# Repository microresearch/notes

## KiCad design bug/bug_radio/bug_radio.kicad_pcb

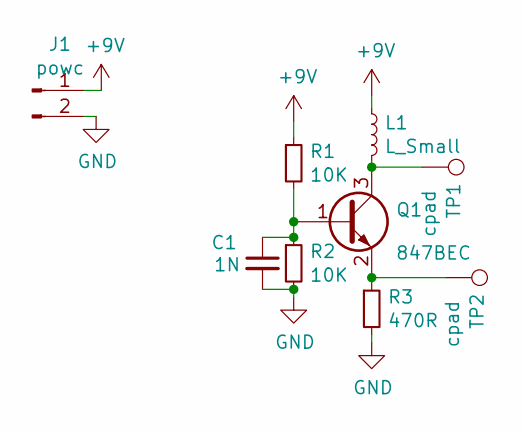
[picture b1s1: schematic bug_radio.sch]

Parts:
C1: 1N; C_0805_HandSoldering
J1: powc; Pin_Header_Straight_1x02_Pitch2.54mm
L1: L_Small; Pin_Header_Straight_1x02_Pitch2.54mm_SMD_Pin1Left
Q1: 847BEC; SOT-23
R1, R2: 10K; R_0805_HandSoldering
R3: 470R; R_0805_HandSoldering
TP1, TP2: cpad; Pin_Header_Straight_1x01_Pitch2.54mm

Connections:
+9V: J1.1, L1.1, R1.1
GND: C1.2, J1.2, R2.2, R3.2
unnamed: C1.1, Q1.1 (B), R1.2, R2.1
unnamed: L1.2, Q1.3 (C), TP1.1
unnamed 4: Q1.2 (E), R3.1, TP2.1; also elsewhere on the board

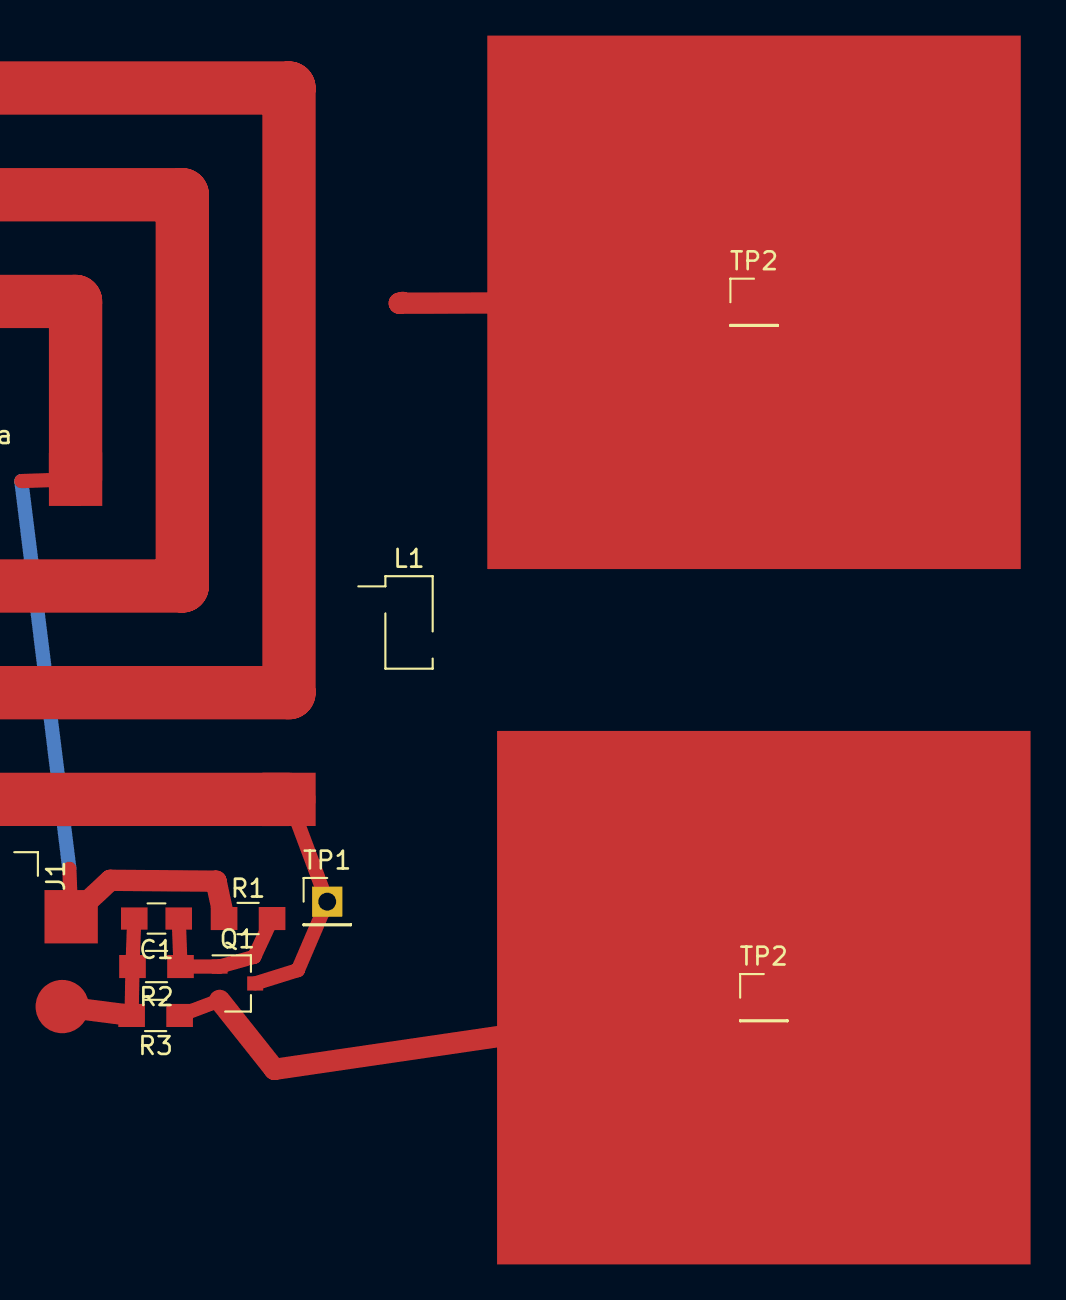
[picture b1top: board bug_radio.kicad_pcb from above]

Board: 2 copper layers, 10 parts (0 on the bottom side), 5 nets.

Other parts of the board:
TP2#2: cpad; Pin_Header_Straight_1x01_Pitch2.54mm

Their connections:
unnamed 4: TP2#2.1; also elsewhere on the board

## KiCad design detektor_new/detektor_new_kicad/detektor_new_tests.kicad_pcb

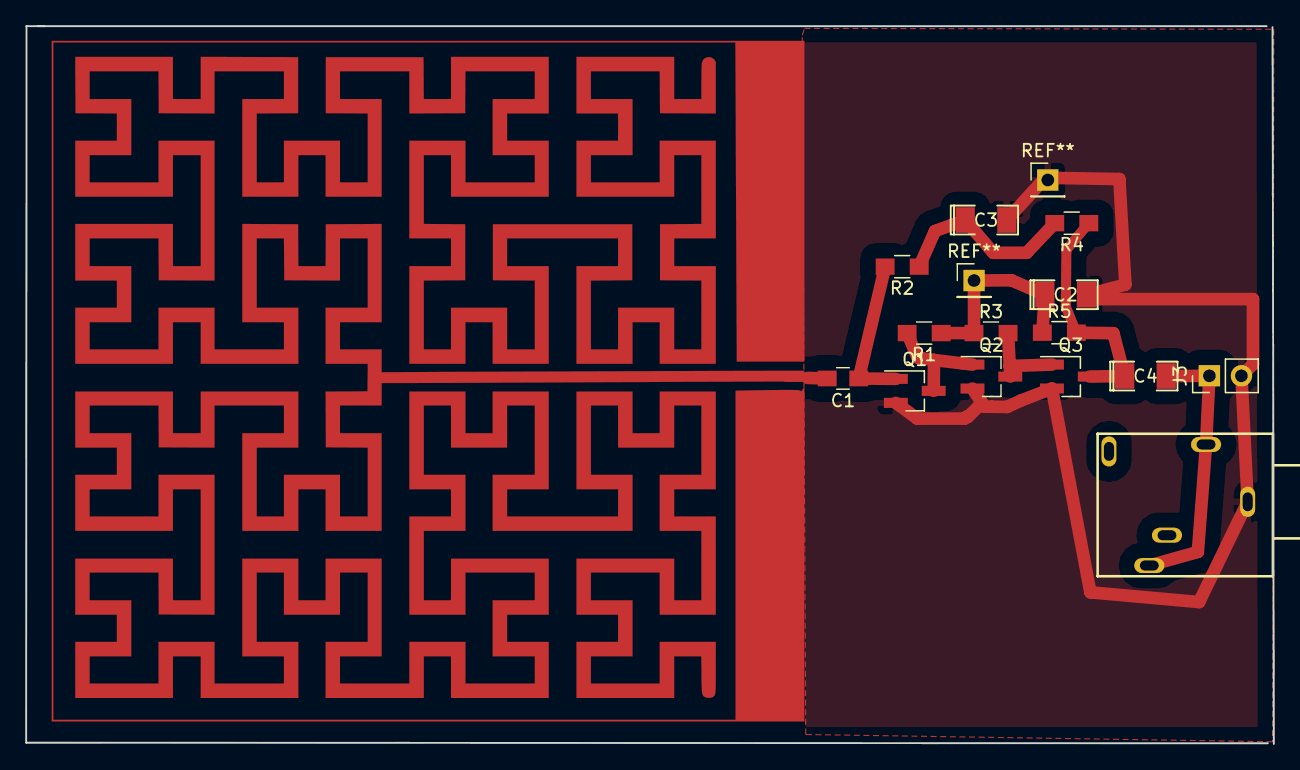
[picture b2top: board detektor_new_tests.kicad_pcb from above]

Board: 2 copper layers, 99.0 x 56.9 mm, 14 parts (0 on the bottom side), 8 nets.

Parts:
C1: 100n; C_0805_HandSoldering
C2, C3, C4: 10u; SMD-1206_Pol
J3: OUT; Pin_Header_Straight_1x02_Pitch2.54mm
Q1: 517-BEC; SOT-23_Handsoldering
Q2, Q3: 847-BEC; SOT-23_Handsoldering
R1, R3: 10K; R_0805_HandSoldering
R2, R4: 100K; R_0805_HandSoldering
R5: 1K; R_0805_HandSoldering
X1: 1503_09

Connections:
GND: C2.2, C3.2, J3.2, Q1.2, Q2.2, Q3.2, X1.1
unnamed: C1.1, Q1.1, R2.2
unnamed: C2.1, R1.1, R3.1, R5.1
unnamed: C3.1, R2.1, R4.2
unnamed: C4.1, Q3.3, R4.1, R5.2
unnamed: C4.2, J3.1, X1.2, X1.3
unnamed: Q1.3, Q2.1, R1.2
unnamed: Q2.3, Q3.1, R3.2

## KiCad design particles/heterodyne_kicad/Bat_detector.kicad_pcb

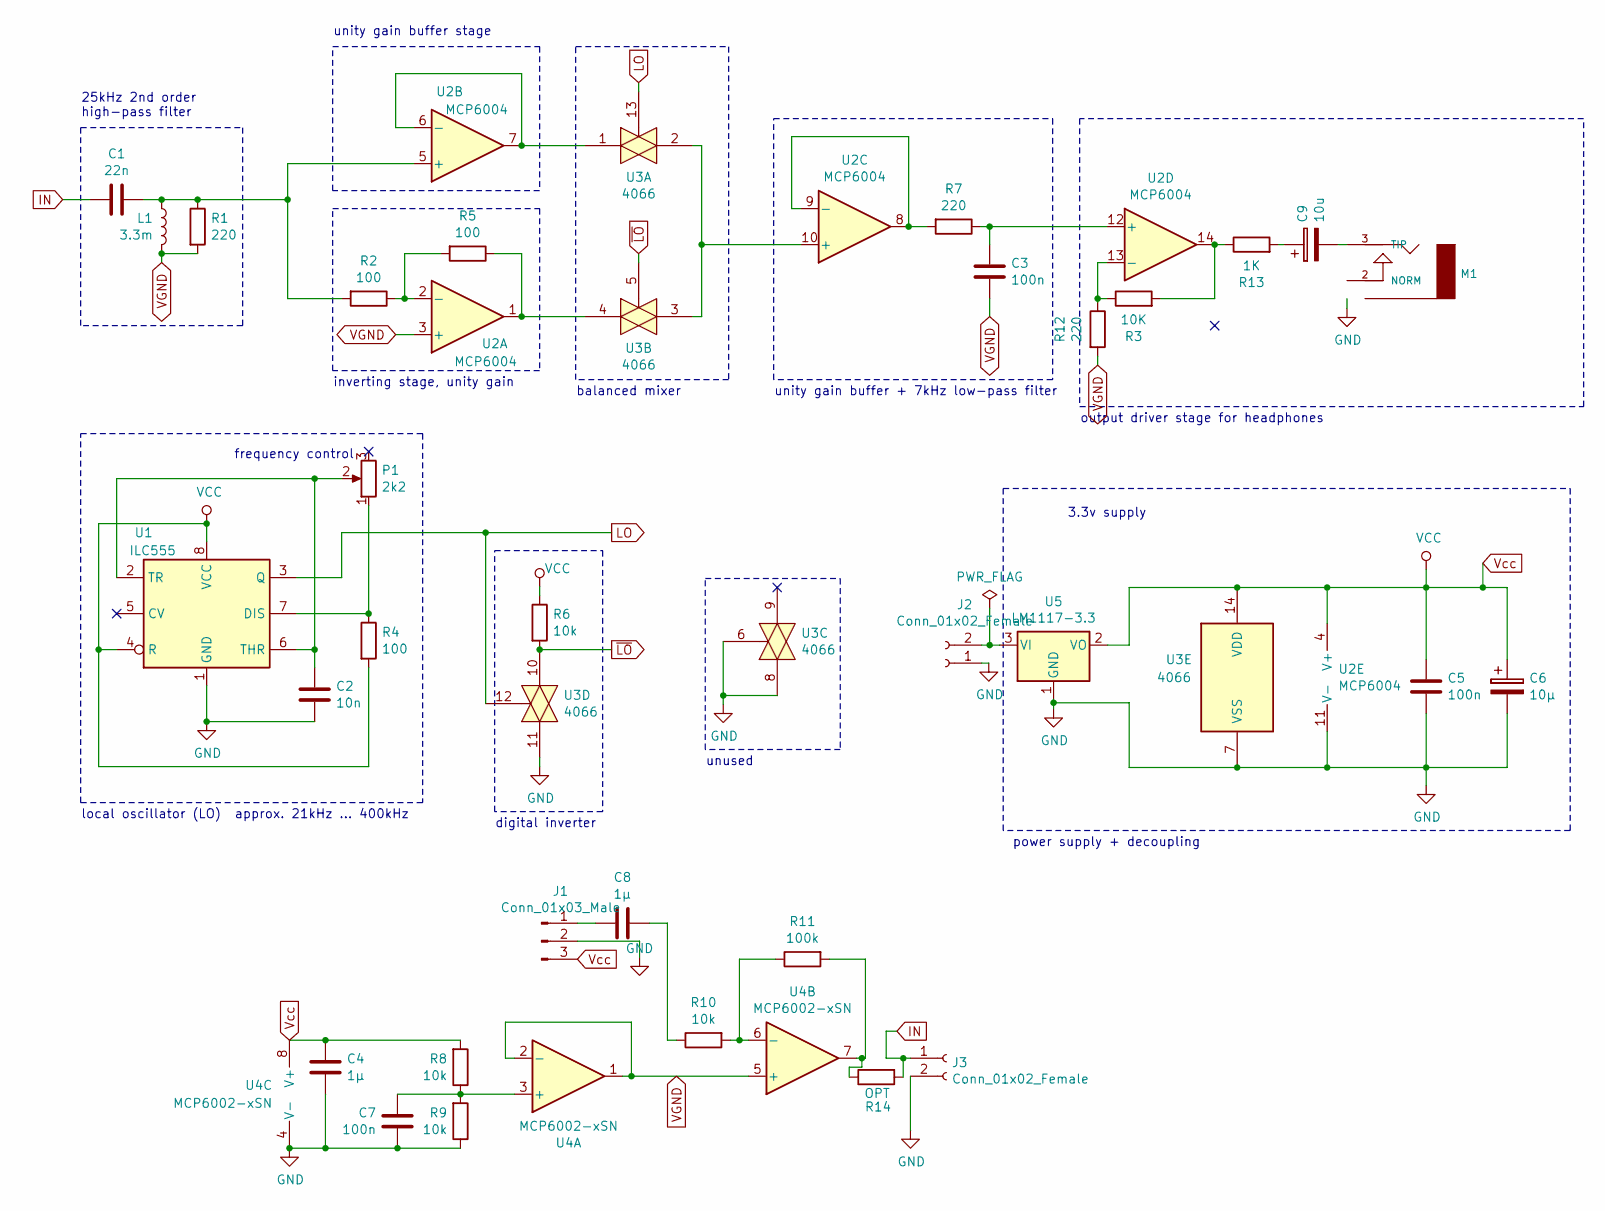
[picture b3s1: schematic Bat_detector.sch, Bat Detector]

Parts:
C1: 22n; C_0805_HandSoldering
C2: 10n; C_0805_HandSoldering
C3, C5, C7: 100n; C_0805_HandSoldering
C4, C8: 1µ; SMD-1206_Pol
C6: 10µ; SMD-1206_Pol
C9: 10u; SMD-1206_Pol
J1: Conn_01x03_Male; Pin_Header_Straight_1x03_Pitch2.54mm
J2, J3: Conn_01x02_Female; Pin_Header_Straight_1x02_Pitch2.54mm
L1: 3.3m; L_Wuerth_HCI-5040
M1: AUDIO-JACKERTHENVAR-PJ398; Jack_3.5mm_QingPu_WQP-PJ398SM_Vertical_CircularHoles
P1: 2k2; Potentiometer_Trimmer_Piher_PT-10v10_Horizontal_Px10.0mm_Py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
R1, R7, R12: 220; R_0805_HandSoldering
R2, R4, R5: 100; R_0805_HandSoldering
R3: 10K; R_0805_HandSoldering
R6, R8, R9, R10: 10k; R_0805_HandSoldering
R11: 100k; R_0805_HandSoldering
R13: 1K; R_0805_HandSoldering
R14: OPT; R_0805_HandSoldering
U1: ILC555; SOIC-8-N
U2: MCP6004; SOIC-14_N
U3: 4066; SOIC-14_N
U4: MCP6002-xSN; SOIC-8-N
U5: LM1117-3.3; TO-252-2_Rectifier

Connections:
GND: C2.2, C4.2, C5.2, C6.2, C7.1, J1.2, J2.1, J3.2, M1.1 (RING), R9.1, U1.1 (GND), U2.11 (V-), U3.6, U3.7 (VSS), U3.8, U3.11, U4.4 (V-), U5.1 (GND)
IN: C1.2, J3.1, R14.2
LO: U1.3 (Q), U3.12, U3.13
unnamed: C1.1, L1.2, R1.1, R2.2, U2.5 (+)
unnamed: C2.1, P1.2, U1.2 (TR), U1.6 (THR)
unnamed: C3.1, R7.1, U2.12 (+)
unnamed: C7.2, R8.1, R9.2, U4.3 (+)
unnamed: C8.1, J1.1
unnamed: C8.2, R10.1
unnamed: C9.1, R13.2
unnamed: C9.2, M1.3 (TIP)
unnamed: J2.2, U5.3 (VI)
unnamed: P1.1, R4.1, U1.7 (DIS)
unnamed: R2.1, R5.2, U2.2 (-)
unnamed: R5.1, U2.1, U3.4
unnamed: R7.2, U2.8, U2.9 (-)
unnamed: R10.2, R11.1, U4.6 (-)
unnamed: R11.2, R14.1, U4.7
unnamed: R3.1, R12.1, U2.13 (-)
unnamed: R3.2, R13.1, U2.14
unnamed: U2.6 (-), U2.7, U3.1
unnamed: U2.10 (+), U3.2, U3.3
VGND: C3.2, L1.1, R1.2, R12.2, U2.3 (+), U4.1, U4.2 (-), U4.5 (+)
Vcc: C4.1, C5.1, C6.1, J1.3, R4.2, R6.1, R8.2, U1.4 (R), U1.8 (VCC), U2.4 (V+), U3.14 (VDD), U4.8 (V+), U5.2 (VO)
~LO: R6.2, U3.5, U3.10

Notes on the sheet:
25kHz 2nd order high-pass filter
inverting stage, unity gain
local oscillator (LO) approx. 21kHz ... 400kHz
digital inverter
unused
balanced mixer
unity gain buffer stage
unity gain buffer + 7kHz low-pass filter
output driver stage for headphones
frequency control
power supply + decoupling
3.3v supply

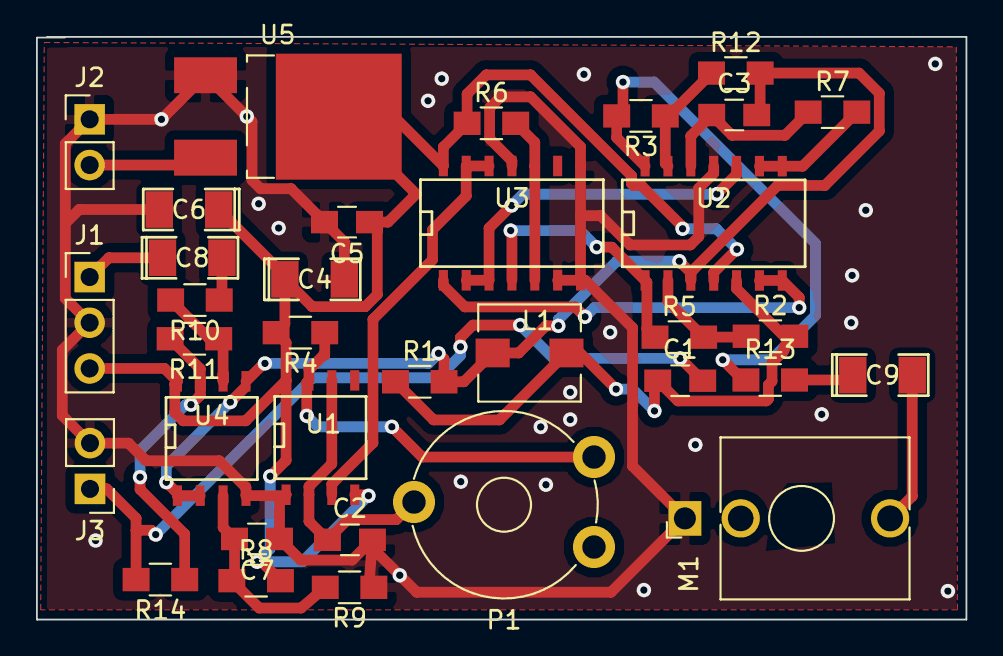
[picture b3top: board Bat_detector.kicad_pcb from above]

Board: 2 copper layers, 51.6 x 32.4 mm, 34 parts (0 on the bottom side), 25 nets.

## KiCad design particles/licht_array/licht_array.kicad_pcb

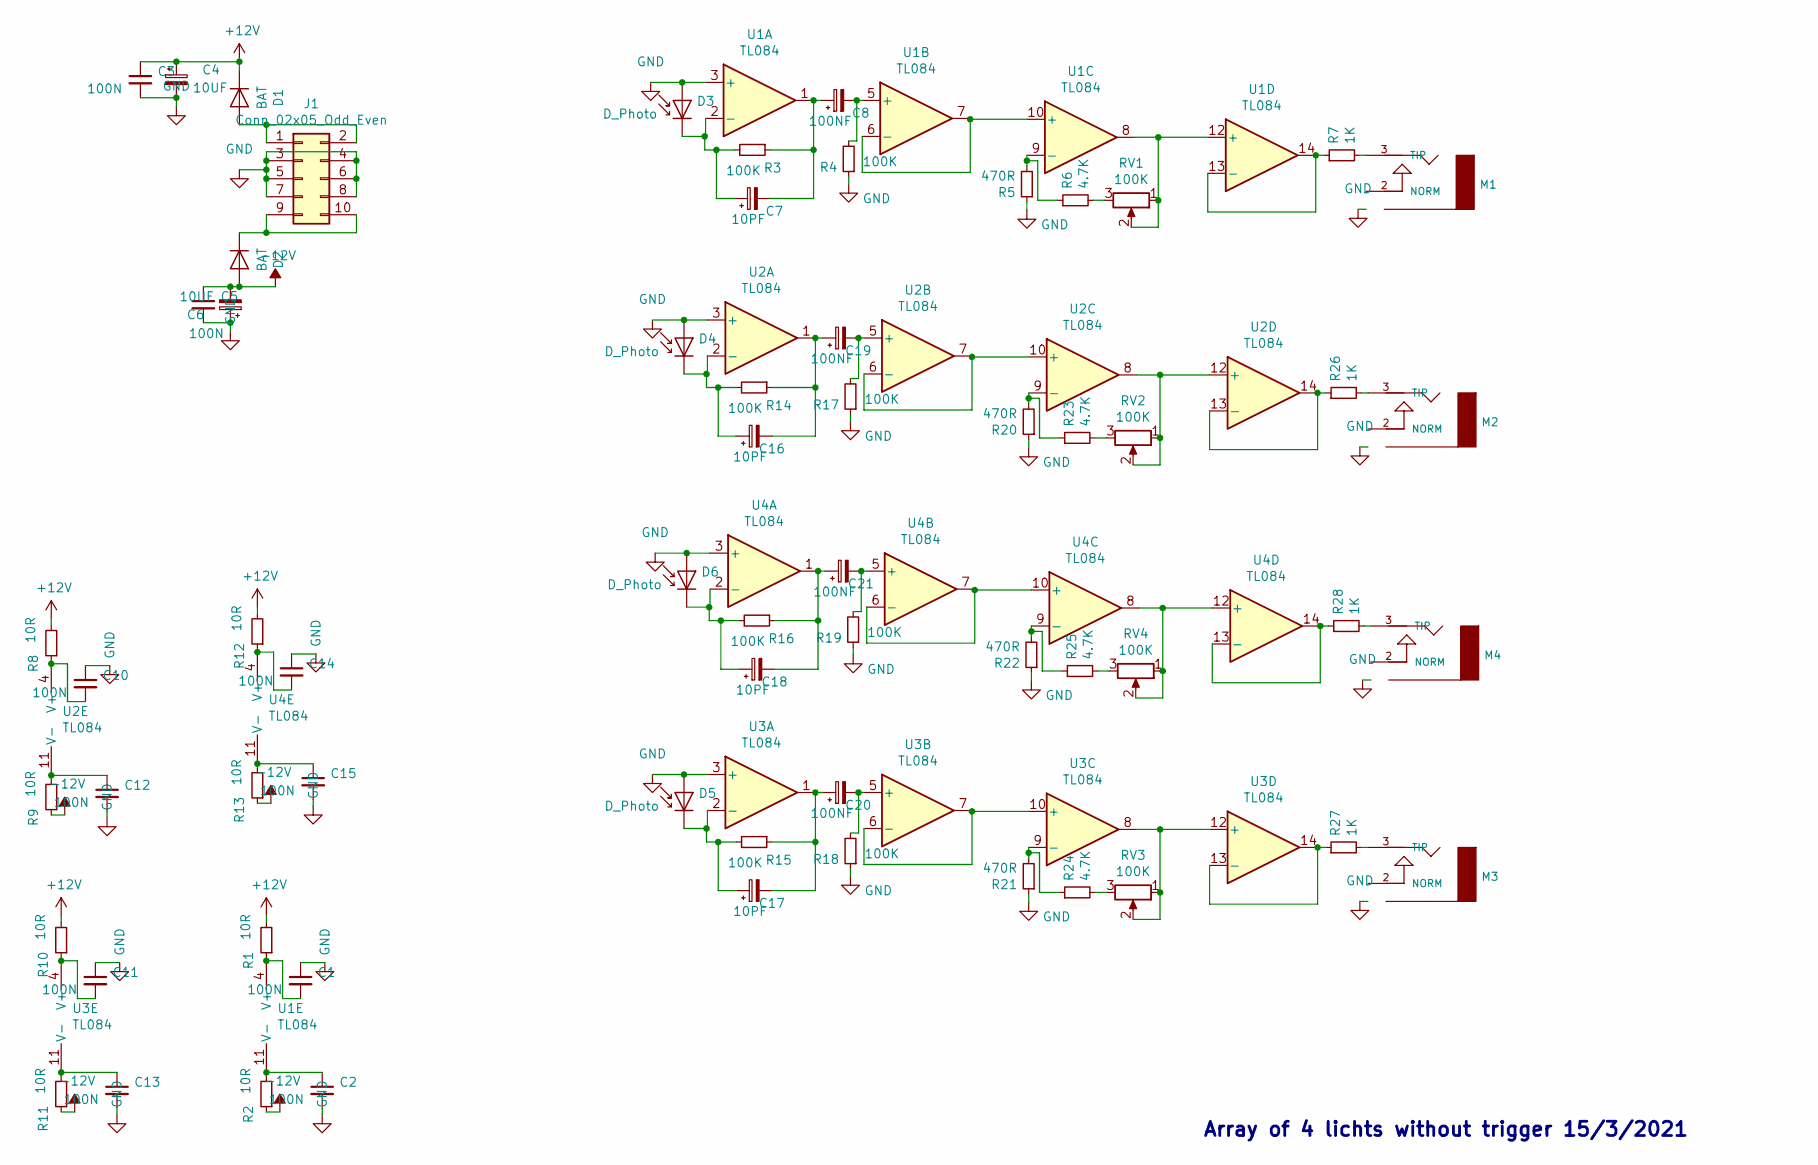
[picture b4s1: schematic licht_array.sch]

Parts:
C1, C2, C3, C5, C10, C11, C12, C13, C14, C15: 100N; C_0805_HandSoldering
C4, C6: 10UF; SMD-1206_Pol
C7, C16, C17, C18: 10PF; C_0805_HandSoldering
C8, C19, C20, C21: 100NF; C_0805_HandSoldering
D1, D2: BAT; D_SOD-123
D3, D4, D5, D6: D_Photo; PhotoDiode_BPW82
J1: Conn_02x05_Odd_Even; Pin_Header_Straight_2x05_Pitch2.54mm
M1, M2, M3, M4: AUDIO-JACKERTHENVAR; Jack_3.5mm_QingPu_WQP-PJ398SM_Vertical_CircularHoles
R1, R2, R8, R9, R10, R11, R12, R13: 10R; R_0805_HandSoldering
R3, R4, R14, R15, R16, R17, R18, R19: 100K; R_0805_HandSoldering
R5, R20, R21, R22: 470R; R_0805_HandSoldering
R6, R23, R24, R25: 4.7K; R_0805_HandSoldering
R7, R26, R27, R28: 1K; R_0805_HandSoldering
RV1, RV2, RV3, RV4: 100K; Potentiometer_Trimmer_Piher_PT-10v10_Horizontal_Px10.0mm_Py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
U1, U2, U3, U4: TL084; SOIC-14_N

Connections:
+12V: C3.1, C4.1, D1.1 (K), R1.2, R8.2, R10.2, R12.2
-12V: C5.1, C6.2, D2.2 (A), R2.1, R9.1, R11.1, R13.1
GND: C1.1, C2.2, C3.2, C4.2, C5.2, C6.1, C10.1, C11.1, C12.2, C13.2, C14.1, C15.2, D3.2 (A), D4.2 (A), D5.2 (A), D6.2 (A), J1.3, J1.4, J1.5, J1.6, J1.7, J1.8, M1.1 (RING), M2.1 (RING), M3.1 (RING), M4.1 (RING), R4.1, R5.1, R17.1, R18.1, R19.1, R20.1, R21.1, R22.1, U1.3 (+), U2.3 (+), U3.3 (+), U4.3 (+)
unnamed: C1.2, R1.1, U1.4 (V+)
unnamed: C2.1, R2.2, U1.11 (V-)
unnamed: C7.1, D3.1 (K), R3.2, U1.2 (-)
unnamed: C7.2, C8.1, R3.1, U1.1
unnamed: C8.2, R4.2, U1.5 (+)
unnamed: C10.2, R8.1, U2.4 (V+)
unnamed: C11.2, R10.1, U3.4 (V+)
unnamed: C12.1, R9.2, U2.11 (V-)
unnamed: C13.1, R11.2, U3.11 (V-)
unnamed: C14.2, R12.1, U4.4 (V+)
unnamed: C15.1, R13.2, U4.11 (V-)
unnamed: C16.1, D4.1 (K), R14.2, U2.2 (-)
unnamed: C16.2, C19.1, R14.1, U2.1
unnamed: C17.1, D5.1 (K), R15.2, U3.2 (-)
unnamed: C17.2, C20.1, R15.1, U3.1
unnamed: C18.1, D6.1 (K), R16.2, U4.2 (-)
unnamed: C18.2, C21.1, R16.1, U4.1
unnamed: C19.2, R17.2, U2.5 (+)
unnamed: C20.2, R18.2, U3.5 (+)
unnamed: C21.2, R19.2, U4.5 (+)
unnamed: D1.2 (A), J1.1, J1.2
unnamed: D2.1 (K), J1.9, J1.10
unnamed: M1.3 (TIP), R7.2
unnamed: M2.3 (TIP), R26.2
unnamed: M3.3 (TIP), R27.2
unnamed: M4.3 (TIP), R28.2
unnamed: R5.2, R6.1, U1.9 (-)
unnamed: R6.2, RV1.3
unnamed: R7.1, U1.13 (-), U1.14
unnamed: R20.2, R23.1, U2.9 (-)
unnamed: R21.2, R24.1, U3.9 (-)
unnamed: R22.2, R25.1, U4.9 (-)
unnamed: R23.2, RV2.3
unnamed: R24.2, RV3.3
unnamed: R25.2, RV4.3
unnamed: R26.1, U2.13 (-), U2.14
unnamed: R27.1, U3.13 (-), U3.14
unnamed: R28.1, U4.13 (-), U4.14
unnamed: RV1.1, RV1.2, U1.8, U1.12 (+)
unnamed: RV2.1, RV2.2, U2.8, U2.12 (+)
unnamed: RV3.1, RV3.2, U3.8, U3.12 (+)
unnamed: RV4.1, RV4.2, U4.8, U4.12 (+)
unnamed: U1.6 (-), U1.7, U1.10 (+)
unnamed: U2.6 (-), U2.7, U2.10 (+)
unnamed: U3.6 (-), U3.7, U3.10 (+)
unnamed: U4.6 (-), U4.7, U4.10 (+)

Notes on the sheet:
Array of 4 lichts without trigger 15/3/2021

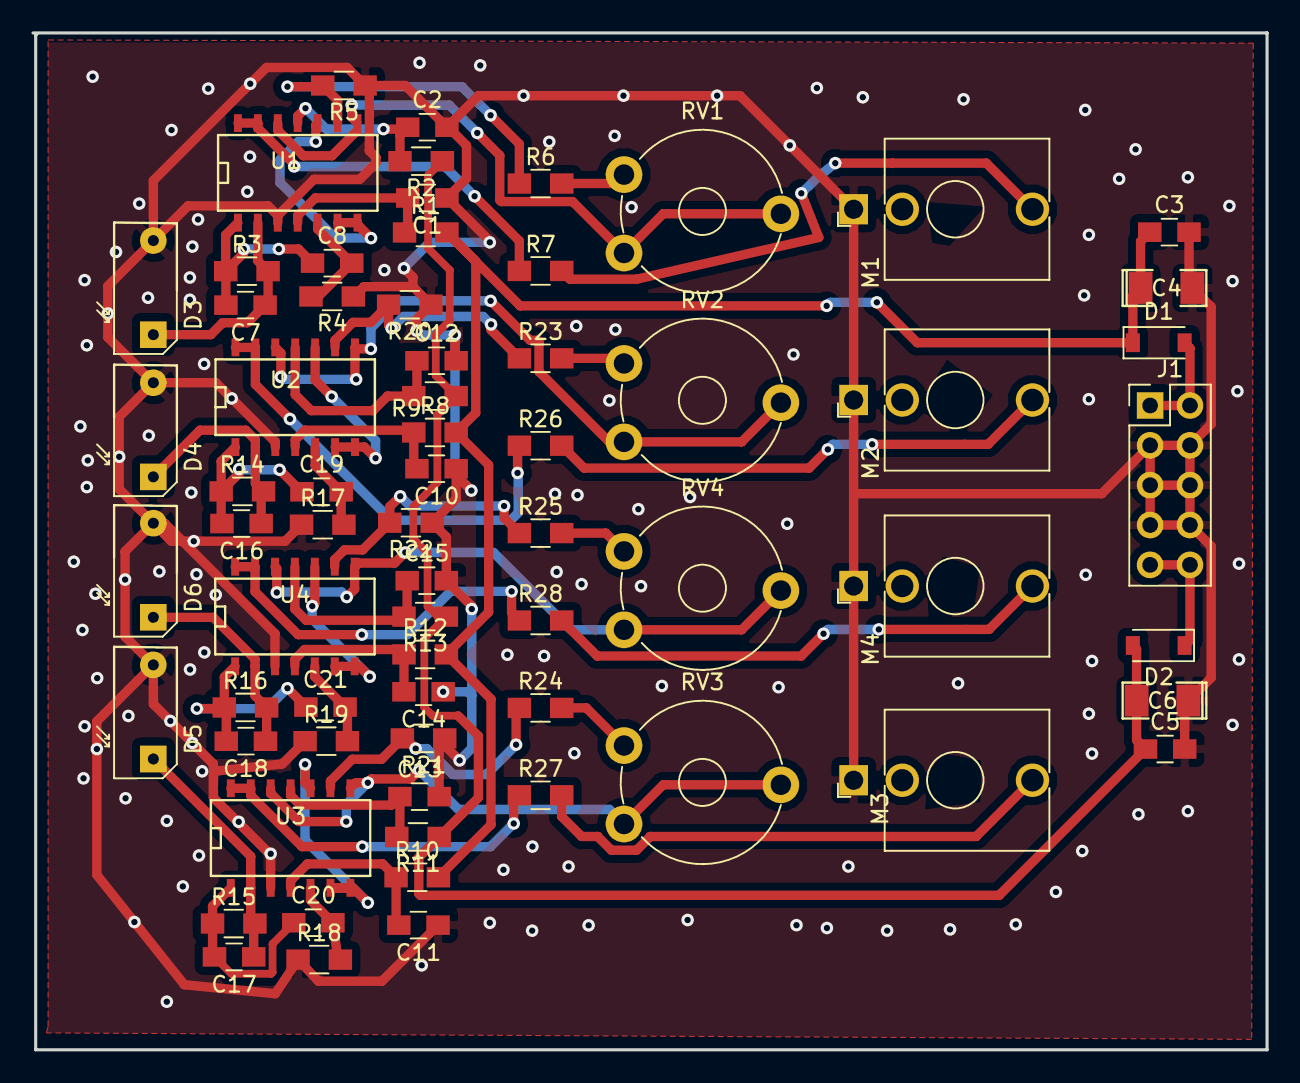
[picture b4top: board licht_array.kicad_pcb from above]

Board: 2 copper layers, 78.7 x 64.8 mm, 67 parts (0 on the bottom side), 49 nets.

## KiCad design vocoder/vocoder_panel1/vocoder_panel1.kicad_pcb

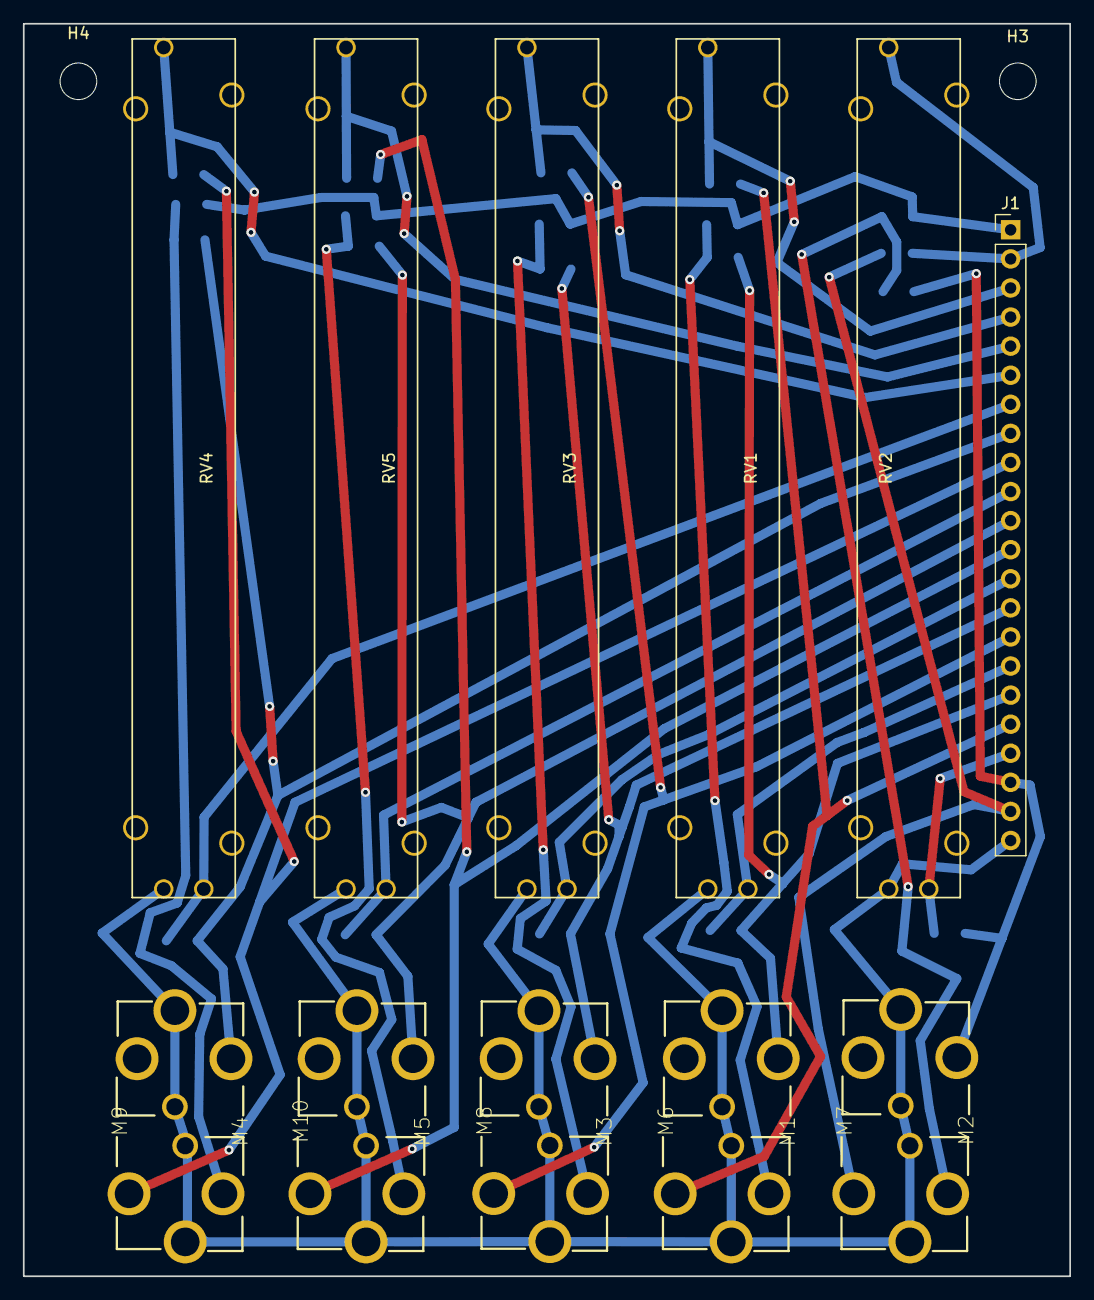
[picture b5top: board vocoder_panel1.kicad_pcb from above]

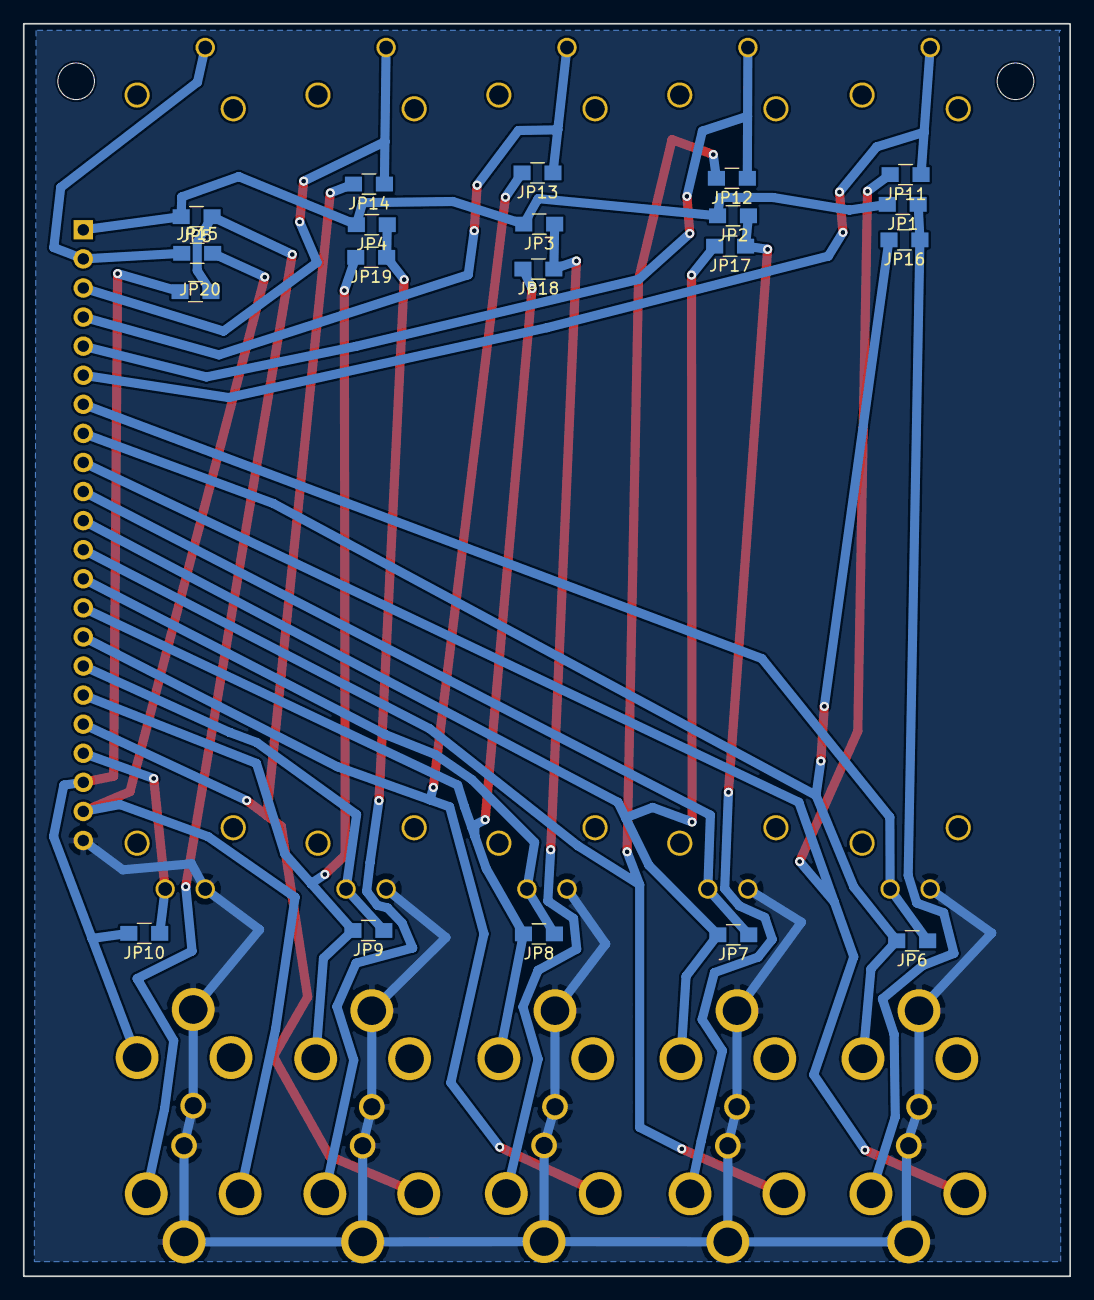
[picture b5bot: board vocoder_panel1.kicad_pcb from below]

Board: 2 copper layers, 91.4 x 109.4 mm, 38 parts (20 on the bottom side), 27 nets.

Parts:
H3, H4: MountingHole; MountingHole_3.2mm_M3
J1: Conn_01x22; Pin_Header_Straight_1x22_Pitch2.54mm
JP1, JP2, JP3, JP4, JP5, JP6, JP7, JP8, JP9, JP10, JP11, JP12, JP13, JP14, JP15, JP16, JP17, JP18, JP19, JP20: Jumper_NO_Small; R_0805_HandSoldering
M1, M2, M3, M4, M5, M6, M7, M8, M9, M10: AUDIO-JACKERTHENVAR; ERTHENVAR-JACK
RV1, RV3, RV4, RV5: R_POT; SMC-PTA6043-2015CPB103new
RV2: R_POT; SMC-PTA6043-2015CPB103

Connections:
/FB1: J1.7, JP6.1, RV4.1
/FB2: J1.10, JP7.1, RV5.1
/FB3: J1.13, JP8.1, RV3.1
/FB4: J1.16, JP9.1, RV1.1
/FB5: J1.19, JP10.1, RV2.1
/FB_1: J1.6, JP11.1, RV4.3
/FB_2: J1.5, JP12.1, RV5.3
/FB_3: J1.4, JP13.1, RV3.3
/FB_4: J1.3, JP14.1, RV1.3
/FB_5: J1.2, JP15.1, RV2.3
/J1: J1.8, JP6.2, JP16.2, M4.3
/J2: J1.11, JP7.2, JP17.2, M5.3
/J3: J1.14, JP8.2, JP18.2, M3.3
/J4: J1.17, JP9.2, JP19.2, M1.3
/J5: J1.20, JP10.2, JP20.2, M2.3
/JJ1: J1.9, JP11.2, M9.3
/JJ2: J1.12, JP12.2, M10.3
/JJ3: J1.15, JP13.2, M8.3
/JJ4: J1.18, JP14.2, M6.3
/JJ5: J1.21, JP15.2, M7.3
/NN1: JP1.1, JP16.1, M9.2
/NN2: JP2.1, JP17.1, M10.2
/NN3: JP3.1, JP18.1, M8.2
/NN4: JP4.1, JP19.1, M6.2
/NN5: JP5.1, JP20.1, M7.2
/PSBUS: J1.1, JP1.2, JP2.2, JP3.2, JP4.2, JP5.2
GND: J1.22, M1.1@1, M1.1@2, M2.1@1, M2.1@2, M3.1@1, M3.1@2, M4.1@1, M4.1@2, M5.1@1, M5.1@2, M6.1@1, M6.1@2, M7.1@1, M7.1@2, M8.1@1, M8.1@2, M9.1@1, M9.1@2, M10.1@1, M10.1@2, RV1.2, RV2.2, RV3.2, RV4.2, RV5.2

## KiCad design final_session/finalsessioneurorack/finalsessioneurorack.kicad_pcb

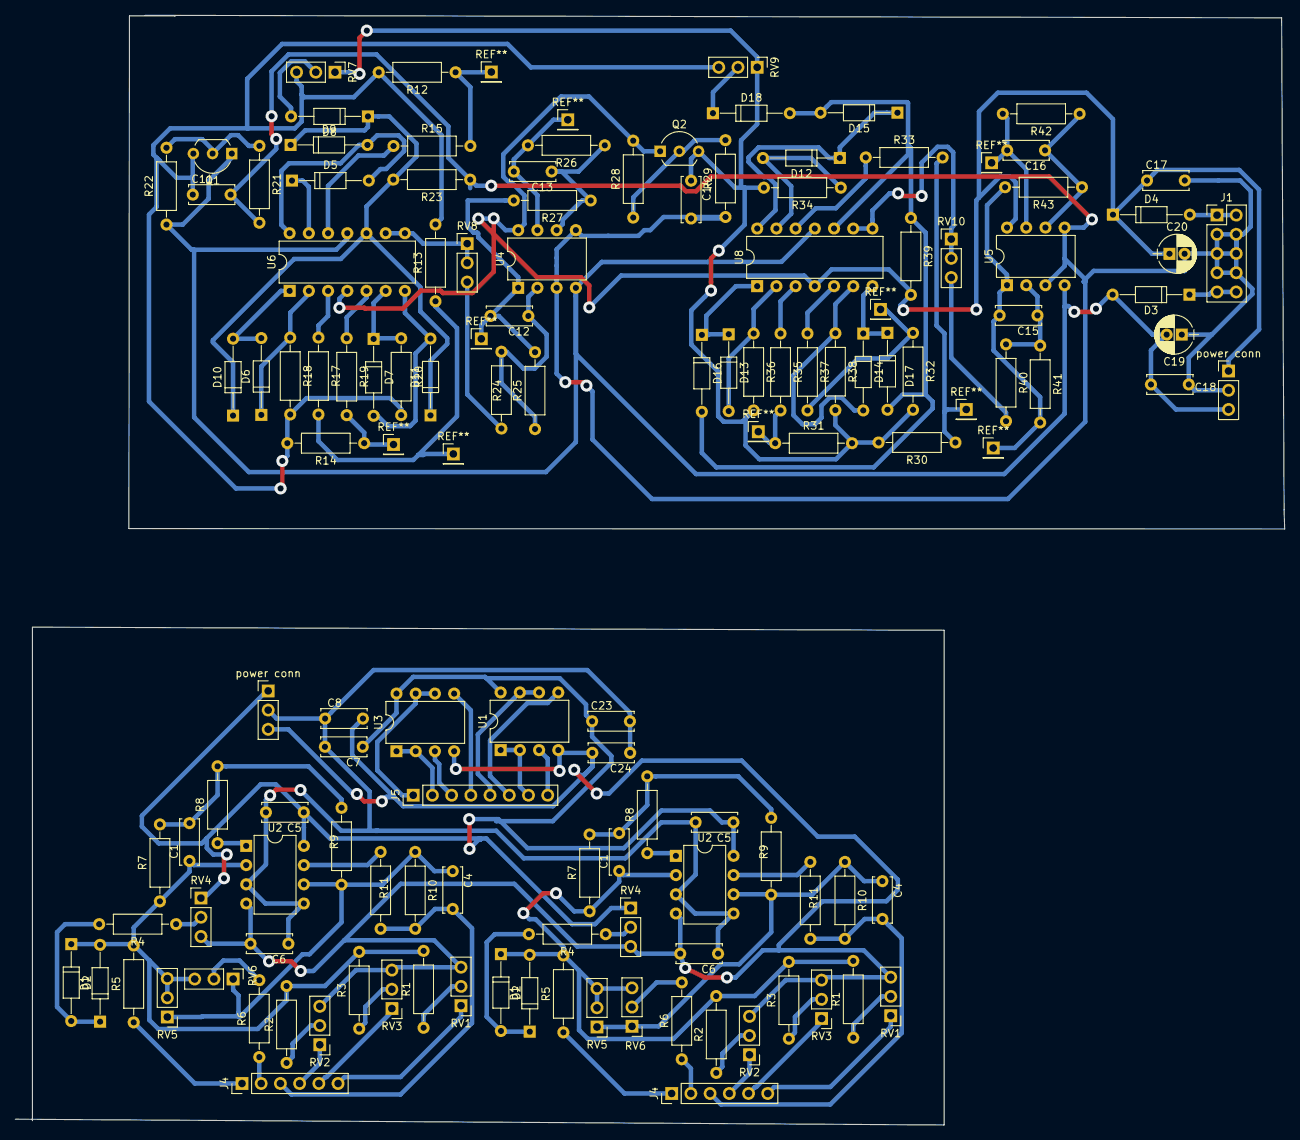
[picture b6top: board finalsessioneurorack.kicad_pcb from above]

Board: 2 copper layers, 167.8 x 146.7 mm, 127 parts (0 on the bottom side), 74 nets.

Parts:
C1, C1#2, C4, C4#2, C12, C13, C15, C16: 47pF; C_Disc_D6.0mm_W2.5mm_P5.00mm
C5, C5#2, C6, C6#2, C7, C8, C17, C18, C23, C24: 100n; C_Disc_D6.0mm_W2.5mm_P5.00mm
C11, C14: 100N; C_Disc_D6.0mm_W2.5mm_P5.00mm
C19, C20: 10uF; CP_Radial_D5.0mm_P2.00mm
D1, D1#2, D2, D2#2: BAT48; D_DO-35_SOD27_P10.16mm_Horizontal
D3, D4: D; D_DO-35_SOD27_P10.16mm_Horizontal
D5, D6, D7, D8, D9, D10, D11, D12, D13, D14, D15, D16, D17, D18: 1N4148; D_DO-35_SOD27_P10.16mm_Horizontal
J1: Conn_02x05_Odd_Even; Pin_Header_Straight_2x05_Pitch2.54mm
J4, J4#2: Conn_01x06_Male; Pin_Header_Straight_1x06_Pitch2.54mm
J5: Conn_01x08_Male; Pin_Header_Straight_1x08_Pitch2.54mm
Q1: BC557; TO-92_Inline_Wide
Q2: BC547; TO-92_Inline_Wide
R1, R1#2, R2, R2#2, R3, R3#2, R5, R5#2, R6, R6#2, R7, R7#2, R9, R9#2, R10, R10#2, R12, R13, R14, R30, R31, R32: 100K; R_Axial_DIN0207_L6.3mm_D2.5mm_P10.16mm_Horizontal
R4, R4#2: 270K; R_Axial_DIN0207_L6.3mm_D2.5mm_P10.16mm_Horizontal
R8, R8#2, R11, R11#2: 330R; R_Axial_DIN0207_L6.3mm_D2.5mm_P10.16mm_Horizontal
R15, R17, R18, R19, R20, R21, R23, R25, R26, R27, R29, R33, R34, R35, R36, R37, R38, R39, R41, R42, R43: 10K; R_Axial_DIN0207_L6.3mm_D2.5mm_P10.16mm_Horizontal
R22, R28: 2K2; R_Axial_DIN0207_L6.3mm_D2.5mm_P10.16mm_Horizontal
R24, R40: 4k7; R_Axial_DIN0207_L6.3mm_D2.5mm_P10.16mm_Horizontal
RV1, RV1#2, RV2, RV2#2, RV3, RV3#2, RV4, RV4#2, RV5, RV5#2, RV6, RV6#2: 100K; Pin_Header_Straight_1x03_Pitch2.54mm
RV7, RV9: R_POT; Pin_Header_Straight_1x03_Pitch2.54mm
RV8, RV10: 10K; Pin_Header_Straight_1x03_Pitch2.54mm
U1, U2, U2#2, U3, U4, U5: TL072; DIP-8_W7.62mm
U6, U8: TL074; DIP-14_W7.62mm
power conn: 100K; Pin_Header_Straight_1x03_Pitch2.54mm
power conn#2: 100K; Pin_Header_Straight_1x03_Pitch2.54mm

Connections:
+12V: C5.1, C5#2.1, C7.1, C17.1, C20.1, C23.1, D4.1, Q2.1, R28.2, R39.2, RV4.1, RV4#2.1, U1.8, U2.8, U2#2.8, U3.8, U4.8, U5.8, U6.4, U8.4, power conn.1, power conn#2.1
-12V: C6.2, C6#2.2, C8.2, C18.2, C19.2, C24.2, D3.2, Q1.1, R22.1, RV1.3, RV1#2.3, RV2.3, RV2#2.3, RV3.3, RV3#2.3, RV4.3, RV4#2.3, U1.4, U2.4, U2#2.4, U3.4, U4.4, U5.4, U6.11, U8.11, power conn.3, power conn#2.3
/INBUF1: J5.8, U1.3
/INBUF2: J5.6, U1.5
/INBUF3: J5.3, U3.3
/INBUF4: J5.4, U3.5
/INN_1: J4.6, J4#2.6, RV1.1, RV1#2.1
/INN_2: J4.4, J4#2.4, RV2.1, RV2#2.1
/INN_3: J4.5, J4#2.5, RV3.1, RV3#2.1
/OBUFF1: J5.7, U1.1, U1.2
/OBUFF2: J5.5, U1.6, U1.7
/OBUFF3: J5.2, U3.1, U3.2
/OBUFF4: J5.1, U3.6, U3.7
/OUTT_1: C4.2, C4#2.2, J4.3, J4#2.3, R10.2, R10#2.2, R11.2, R11#2.2
/P1: J4.1, J4#2.1, R5.1, R5#2.1
/P2: J4.2, J4#2.2, R6.1, R6#2.1
/analogue logic/-10V: C11.1, Q1.3, R12.2, R13.2, R14.2, R18.2, R20.2, RV7.3, RV9.3
/analogue logic/AND: C16.2, R42.2, U5.7
/analogue logic/IN_1: R12.1, R15.2
/analogue logic/IN_1x: R30.1, R33.2
/analogue logic/IN_2: R13.1, R17.2
/analogue logic/IN_2x: R31.1, R35.2
/analogue logic/IN_3: R14.1, R19.2
/analogue logic/IN_3x: R32.1, R37.2
/analogue logic/NAND: C15.2, R41.2, R43.2, U5.1
/analogue logic/NOR: C12.2, R25.2, R27.2, U4.1
/analogue logic/OR: C13.2, R26.2, U4.7
GND: C5.2, C5#2.2, C6.1, C6#2.1, C7.2, C8.1, C11.2, C14.2, C17.2, C18.1, C19.1, C20.2, C23.2, C24.1, J1.3, J1.4, J1.5, J1.6, J1.7, J1.8, R21.2, R23.1, R29.1, U2.3, U2.5, U2#2.3, U2#2.5, U4.3, U4.5, U5.3, U5.5, power conn.2, power conn#2.2
unnamed: C1.1, C1#2.1, D1.2, D1#2.2, D2.1, D2#2.1, R1.2, R1#2.2, R2.2, R2#2.2, R3.2, R3#2.2, R5.2, R5#2.2, R7.1, R7#2.1, RV5.2, RV5.3, RV5#2.2, RV5#2.3, RV6.3, RV6#2.3, U2.2, U2#2.2
unnamed: C1.2, C1#2.2, R7.2, R7#2.2, R8.2, R8#2.2, R9.1, R9#2.1
unnamed: C4.1, C4#2.1, R9.2, R9#2.2, R10.1, R10#2.1, RV5.1, RV5#2.1, RV6.1, RV6#2.1, U2.6, U2#2.6
unnamed: D3.1, J1.9, J1.10
unnamed: D4.2, J1.1, J1.2
unnamed: C12.1, R24.1, R25.1, U4.2
unnamed: C13.1, R26.1, R27.1, U4.6
unnamed: C14.1, Q2.3, R30.2, R31.2, R32.2, R34.2, R36.2, R38.2, RV7.1, RV9.1
unnamed: C15.1, R40.1, R41.1, U5.2
unnamed: C16.1, R42.1, R43.1, U5.6
unnamed: D1.1, D1#2.1, D2.2, D2#2.2, R4.2, R4#2.2
unnamed: D5.1, U6.13
unnamed: D5.2, D9.2, U6.14
unnamed: D6.1, R18.1, U6.2
unnamed: D7.1, R20.1, U6.6
unnamed: D8.2, RV7.2
unnamed: D8.1, D9.1, D10.1, D11.1, R23.2, U6.10
unnamed: D6.2, D10.2, U6.1
unnamed: D7.2, D11.2, U6.7
unnamed: D12.1, D15.1, U8.14
unnamed: D12.2, R34.1, U8.13
unnamed: D13.1, D16.1, U8.1
unnamed: D13.2, R36.1, U8.2
unnamed: D14.1, D17.1, U8.7
unnamed: D14.2, R38.1, U8.6
unnamed: D15.2, D16.2, D17.2, D18.2, R39.1, U8.10
unnamed: D18.1, RV9.2
unnamed: Q1.2, R21.1, R22.2
unnamed: Q2.2, R28.1, R29.2
unnamed: R1.1, R1#2.1, RV1.2, RV1#2.2
unnamed: R2.1, R2#2.1, RV2.2, RV2#2.2
unnamed: R3.1, R3#2.1, RV3.2, RV3#2.2
unnamed: R4.1, R4#2.1, RV4.2, RV4#2.2
unnamed: R6.2, R6#2.2, RV6.2, RV6#2.2
unnamed: R8.1, R8#2.1, U2.1, U2#2.1
unnamed: R11.1, R11#2.1, U2.7, U2#2.7
unnamed: R15.1, U6.12
unnamed: R17.1, U6.3
unnamed: R19.1, U6.5
unnamed: R24.2, RV8.3
unnamed: R33.1, U8.12
unnamed: R35.1, U8.3
unnamed: R37.1, U8.5
unnamed: R40.2, RV10.3
unnamed: RV8.1, RV8.2, U6.8, U6.9
unnamed: RV10.1, RV10.2, U8.8, U8.9

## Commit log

2018-07-11 parts added
2018-08-01 logs from messene
2018-08-01 bremen publication now in git
2018-08-01 tech
2018-08-03 play data
2018-08-06 name change
2018-08-06 heat sick
2018-08-06 added first draft
2018-08-07 closer
2018-08-13 added for internal temp
2018-08-14 fogger
2018-08-22 earthboot software
2018-08-23 add zx
2018-08-24 adding eb zx
2018-09-12 added low light picamera
2018-09-17 fgm3 again
2018-10-24 gold
2018-12-27 low power logging in progress
2019-01-08 finalsessionlogicpcb
2019-01-15 packets
2019-01-16 parts for dusg
2019-01-31 splits
2019-02-07 antenna priezor on one sheet 384x384 formulor
2019-02-07 holes/spacers
2019-03-07 working pi/depletion work
2019-03-26 close
2019-05-03 gps logger for fields, waves
2019-06-10 logg
2019-06-17 fixed
2019-06-18 to extract rng
2019-06-19 randomwalk
2019-06-20 heatsick
2019-06-25 fppp
2019-07-01 heat
2019-07-29 fpga
2019-07-29 TEH installation
2019-08-09 should be latest ouroboric.py
2019-08-14 retalk
2019-08-22 flite
2019-08-27 patch
2019-08-28 lpc not crashing
2019-08-29 setting up TEH
2019-09-10 parts/teh
2019-09-10 ouroboros
2019-09-18 xxlog
2019-09-18 messy
2019-11-07 tiny
2019-12-10 parts
2020-03-04 first potentiostat proof of concept to be tested
2020-03-06 RMA software
2020-03-22 for new writings
2020-03-22 fpga notes
2020-04-14 panels for haible vocoder
2020-04-18 panel
2020-04-24 partcile walker with old school GPS/NMEA and some particle sensor
2020-06-02 new doppler fpga dir
2020-06-10 closing in
2020-06-11 first
2020-06-11 finally
2020-07-15 pilgrim1
2020-10-12 scoot-it
2020-10-13 opencoil
2020-10-13 index.html
2020-10-13 fnal
2020-12-20 fixed panel wiring for channels
2021-03-08 particles control
2021-03-15 heterodyne and licht array x4
2021-03-16 det and array
2021-03-23 cuts
2021-06-01 BUG RADIO
2021-06-03 back panel for smoke particle case
2021-06-04 panel back
2021-06-07 oled code for cosmicwatch altered for our SH1106 OLED
2021-07-14 particle control
2021-07-30 xxxxx
2021-08-05 contig/new solstice plotting softwares
2021-08-28 backsmoke.pdf
2021-08-30 syyy
2021-09-13 INCANTATION
2021-09-15 permute
2021-09-16 MOON!USB!
2021-12-08 Beckett gray
2022-01-10 ballardmatcher
2022-02-19 VOID Tenerife
2022-04-08 island
2022-07-21 cores
